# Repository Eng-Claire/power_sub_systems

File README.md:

Welcome to the MicroMouse project kiCAD files of Chidochashe Kufakunesu ( KFKCHI001) and Danella Oelofse ( OLFDAN001 )

The folder titled 'FinalMicroMouseFiles' is the final version of our project and the version that was submitted to UCT. It includes a screenshot of the JLCPCB cart, the BOM, the positions file, as well as the gerber and drill files from kiCAD.

The zip folder is the kiCAD gerber files that were submitted to JLCPCB for manufacturing.

The pdf entitled 'FinalSchematic' is the schematic of our entire solution for the power subsystem.

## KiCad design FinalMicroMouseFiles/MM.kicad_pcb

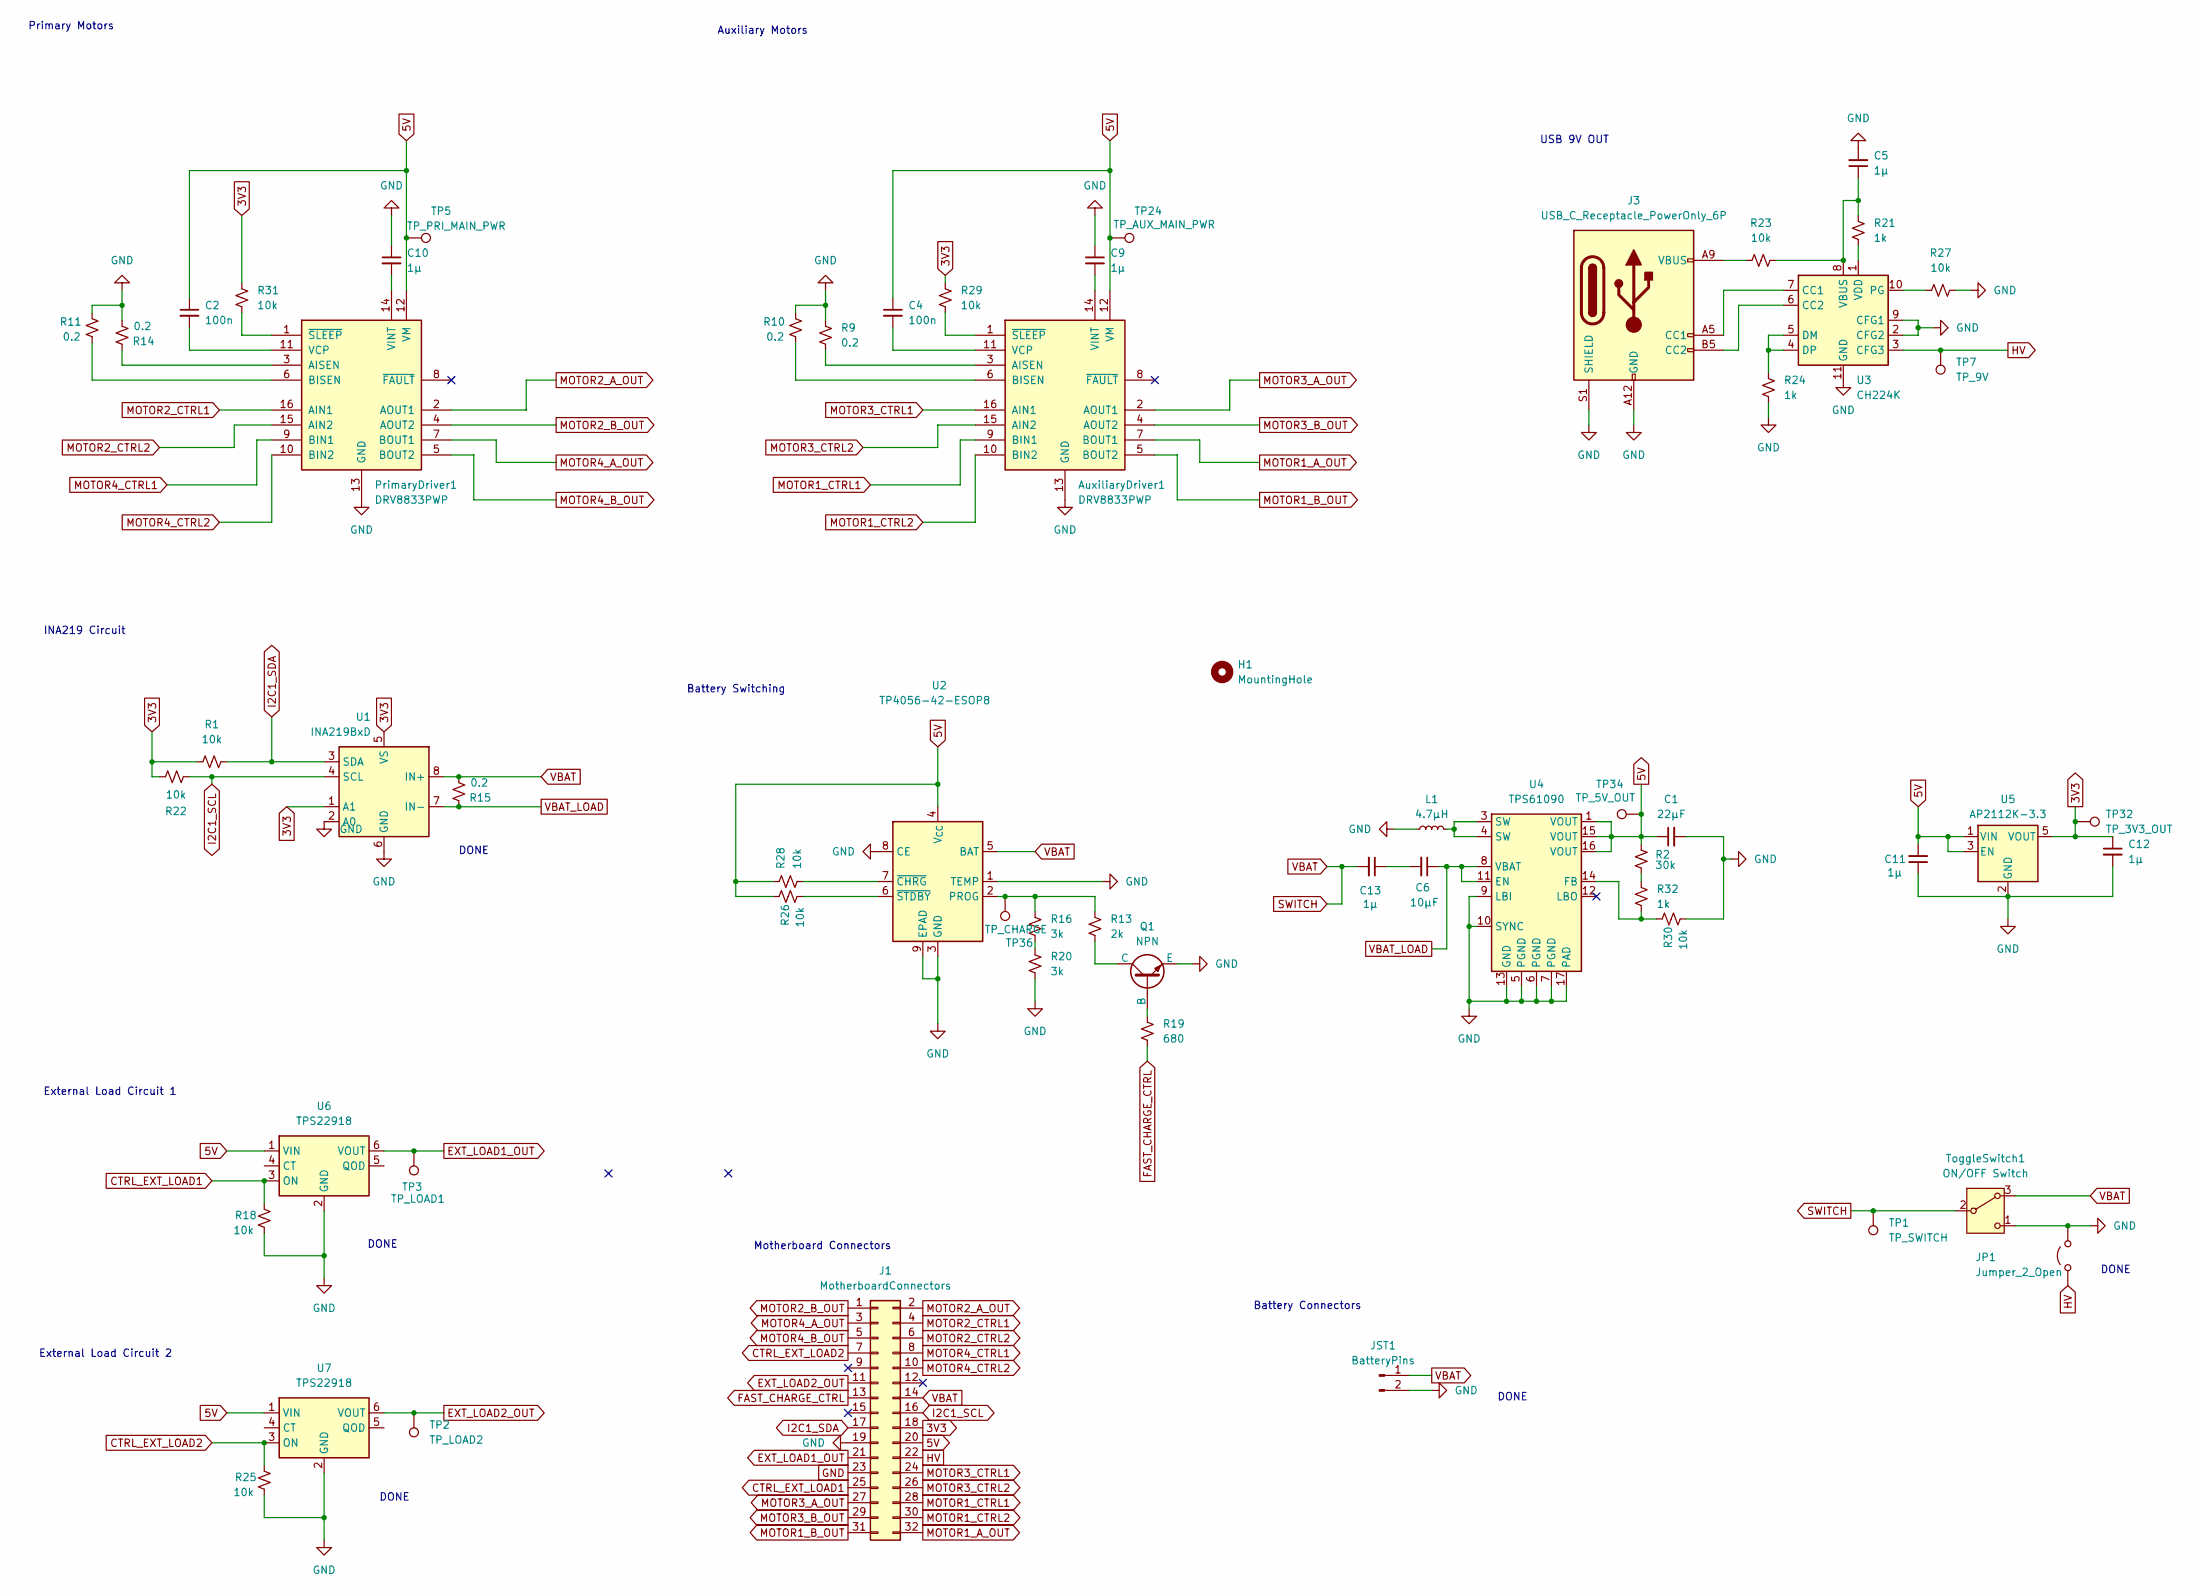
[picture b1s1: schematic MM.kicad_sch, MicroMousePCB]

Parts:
AuxiliaryDriver1: DRV8833PWP; TSSOP-16-1EP_4.4x5mm_P0.65mm_EP3x3mm_ThermalVias; LCSC C50506
C1: 22µF; C_0805_2012Metric_Pad1.18x1.45mm_HandSolder; LCSC C45783
C2, C4: 100n; C_0402_1005Metric; LCSC C1525
C5, C9, C10, C11, C12, C13: 1μ; C_0504_1310Metric_Pad0.83x1.28mm_HandSolder; LCSC C15849
C6: 10µF; C_1206_3216Metric_Pad1.33x1.80mm_HandSolder; LCSC C13585
H1: MountingHole; MountingHole_3.2mm_M3_DIN965_Pad
J1: MotherboardConnectors; PinHeader_2x16_P2.54mm_Vertical
J3: USB_C_Receptacle_PowerOnly_6P; USB_C_Receptacle_GCT_USB4125-xx-x-0190_6P_TopMnt_Horizontal; LCSC C668623
JP1: Jumper_2_Open; TestPoint_2Pads_Pitch2.54mm_Drill0.8mm
JST1: BatteryPins; JST_PH_B2B-PH-K_1x02_P2.00mm_Vertical; LCSC C157955
L1: 4.7µH; L_0603_1608Metric_Pad1.05x0.95mm_HandSolder; LCSC C114862
PrimaryDriver1: DRV8833PWP; TSSOP-16-1EP_4.4x5mm_P0.65mm_EP3x3mm_ThermalVias; LCSC C50506
Q1: NPN; TO-92; LCSC C5330385
R1, R18, R22, R23, R25, R26, R27, R28, R29, R30, R31: 10k; R_0805_2012Metric_Pad1.20x1.40mm_HandSolder; LCSC C17414
R2: 30k; R_0603_1608Metric_Pad0.98x0.95mm_HandSolder; LCSC C22984
R9, R10, R11, R14, R15: 0.2; R_0805_2012Metric; LCSC C2934262
R13: 2k; R_0603_1608Metric_Pad0.98x0.95mm_HandSolder; LCSC C22975
R16, R20: 3k; R_0603_1608Metric_Pad0.98x0.95mm_HandSolder; LCSC C4211
R19: 680; R_0603_1608Metric_Pad0.98x0.95mm_HandSolder; LCSC C23228
R21, R24, R32: 1k; R_0402_1005Metric; LCSC C11702
TP1: TP_SWITCH; TestPoint_Pad_D2.0mm
TP2: TP_LOAD2; TestPoint_Pad_D2.0mm
TP3: TP_LOAD1; TestPoint_Pad_D2.0mm
TP5: TP_PRI_MAIN_PWR; TestPoint_Pad_D2.0mm
TP7: TP_9V; TestPoint_Pad_D2.0mm
TP24: TP_AUX_MAIN_PWR; TestPoint_Pad_D2.0mm
TP32: TP_3V3_OUT; TestPoint_Pad_D2.0mm
TP34: TP_5V_OUT; TestPoint_Pad_D2.0mm
TP36: TP_CHARGE; TestPoint_Pad_D2.0mm
ToggleSwitch1: ON/OFF Switch; SW_SPDT_CK_JS102011SAQN; LCSC C1788492
U1: INA219BxD; SOIC-8-1EP_3.9x4.9mm_P1.27mm_EP2.29x3mm; LCSC C138706
U2: TP4056-42-ESOP8; SOIC-8-1EP_3.9x4.9mm_P1.27mm_EP2.41x3.3mm_ThermalVias; LCSC C16581
U3: CH224K; SSOP-10-1EP_3.9x4.9mm_P1mm_EP2.1x3.3mm; LCSC C970725
U4: TPS61090; Texas_RSA_VQFN-16-1EP_4x4mm_P0.65mm_EP2.7x2.7mm_ThermalVias; LCSC C206167
U5: AP2112K-3.3; SOT-23-5; LCSC C3021085
U6, U7: TPS22918; SOT-23-6; LCSC C131941

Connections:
3V3: C12.1, J1.18, R1.1, R22.2, R29.1, R31.1, TP32.1, U1.1 (A1), U1.5 (VS), U5.5 (VOUT)
5V: AuxiliaryDriver1.12 (VM), C1.1, C2.1, C4.1, C11.2, J1.20, PrimaryDriver1.12 (VM), R2.1, R26.1, R28.1, TP5.1, TP24.1, TP34.1, U2.4 (V_{CC}), U4.1 (VOUT), U4.15 (VOUT), U4.16 (VOUT), U5.1 (VIN), U5.3 (EN), U6.1 (VIN), U7.1 (VIN)
CTRL_EXT_LOAD1: J1.25, R18.1, U6.3 (ON)
CTRL_EXT_LOAD2: J1.7, R25.1, U7.3 (ON)
EXT_LOAD1_OUT: J1.21, TP3.1, U6.6 (VOUT)
EXT_LOAD2_OUT: J1.11, TP2.1, U7.6 (VOUT)
FAST_CHARGE_CTRL: J1.13, R19.2
GND: AuxiliaryDriver1.13 (GND), AuxiliaryDriver1.17 (GND), C1.2, C5.2, C9.1, C10.1, C11.1, C12.2, J1.19, J1.23, J3.A12 (GND), J3.B12 (GND), J3.S1 (SHIELD), JP1.2 (B), JST1.2, L1.1, PrimaryDriver1.13 (GND), PrimaryDriver1.17 (GND), Q1.3 (E), R9.2, R10.2, R11.2, R14.1, R18.2, R20.2, R24.2, R25.2, R27.2, R30.2, ToggleSwitch1.1 (C), U1.2 (A0), U1.6 (GND), U2.1 (TEMP), U2.3 (GND), U2.8 (CE), U2.9 (EPAD), U3.2 (CFG2), U3.9 (CFG1), U3.11 (GND), U4.5 (PGND), U4.6 (PGND), U4.7 (PGND), U4.9 (LBI), U4.10 (SYNC), U4.13 (GND), U4.17 (PAD), U5.2 (GND), U6.2 (GND), U7.2 (GND)
HV: J1.22, JP1.1 (A), TP7.1, U3.3 (CFG3)
I2C1_SCL: J1.16, R22.1, U1.4 (SCL)
I2C1_SDA: J1.17, R1.2, U1.3 (SDA)
MOTOR1_A_OUT: AuxiliaryDriver1.7 (BOUT1), J1.32
MOTOR1_B_OUT: AuxiliaryDriver1.5 (BOUT2), J1.31
MOTOR1_CTRL1: AuxiliaryDriver1.9 (BIN1), J1.28
MOTOR1_CTRL2: AuxiliaryDriver1.10 (BIN2), J1.30
MOTOR2_A_OUT: J1.2, PrimaryDriver1.2 (AOUT1)
MOTOR2_B_OUT: J1.1, PrimaryDriver1.4 (AOUT2)
MOTOR2_CTRL1: J1.4, PrimaryDriver1.16 (AIN1)
MOTOR2_CTRL2: J1.6, PrimaryDriver1.15 (AIN2)
MOTOR3_A_OUT: AuxiliaryDriver1.2 (AOUT1), J1.27
MOTOR3_B_OUT: AuxiliaryDriver1.4 (AOUT2), J1.29
MOTOR3_CTRL1: AuxiliaryDriver1.16 (AIN1), J1.24
MOTOR3_CTRL2: AuxiliaryDriver1.15 (AIN2), J1.26
MOTOR4_A_OUT: J1.3, PrimaryDriver1.7 (BOUT1)
MOTOR4_B_OUT: J1.5, PrimaryDriver1.5 (BOUT2)
MOTOR4_CTRL1: J1.8, PrimaryDriver1.9 (BIN1)
MOTOR4_CTRL2: J1.10, PrimaryDriver1.10 (BIN2)
unnamed: AuxiliaryDriver1.3 (AISEN), R9.1
unnamed: AuxiliaryDriver1.6 (BISEN), R10.1
unnamed: AuxiliaryDriver1.11 (VCP), C4.2
unnamed: AuxiliaryDriver1.14 (VINT), C9.2
unnamed: AuxiliaryDriver1.1 (~SLEEP), R29.2
unnamed: C6.2, C13.1
unnamed: J3.A5 (CC1), U3.7 (CC1)
unnamed: J3.B5 (CC2), U3.6 (CC2)
unnamed: J3.A9 (VBUS), J3.B9 (VBUS), R23.1
unnamed: L1.2, U4.3 (SW), U4.4 (SW)
unnamed: PrimaryDriver1.3 (AISEN), R14.2
unnamed: PrimaryDriver1.6 (BISEN), R11.1
unnamed: C2.2, PrimaryDriver1.11 (VCP)
unnamed: C10.2, PrimaryDriver1.14 (VINT)
unnamed: PrimaryDriver1.1 (~SLEEP), R31.2
unnamed: Q1.2 (B), R19.1
unnamed: Q1.1 (C), R13.2
unnamed: R2.2, R32.1
unnamed: R16.2, R20.1
unnamed: R13.1, R16.1, TP36.1, U2.2 (PROG)
unnamed: R28.2, U2.7 (~CHRG)
unnamed: R26.2, U2.6 (~STDBY)
unnamed: R24.1, U3.4 (DP), U3.5 (DM)
unnamed: R27.1, U3.10 (PG)
unnamed: C5.1, R21.1, R23.2, U3.8 (VBUS)
unnamed: R21.2, U3.1 (VDD)
unnamed: R30.1, R32.2, U4.14 (FB)
SWITCH: C13.2, J1.14, JST1.1, R15.1, TP1.1, ToggleSwitch1.2 (B), ToggleSwitch1.3 (A), U1.8 (IN+), U2.5 (BAT)
VBAT_LOAD: C6.1, R15.2, U1.7 (IN-), U4.8 (VBAT), U4.11 (EN)

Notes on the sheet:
Primary Motors
DONE
External Load Circuit 1
Motherboard Connectors
INA219 Circuit
Battery Connectors
Auxiliary Motors
External Load Circuit 2
USB 9V OUT
Battery Switching

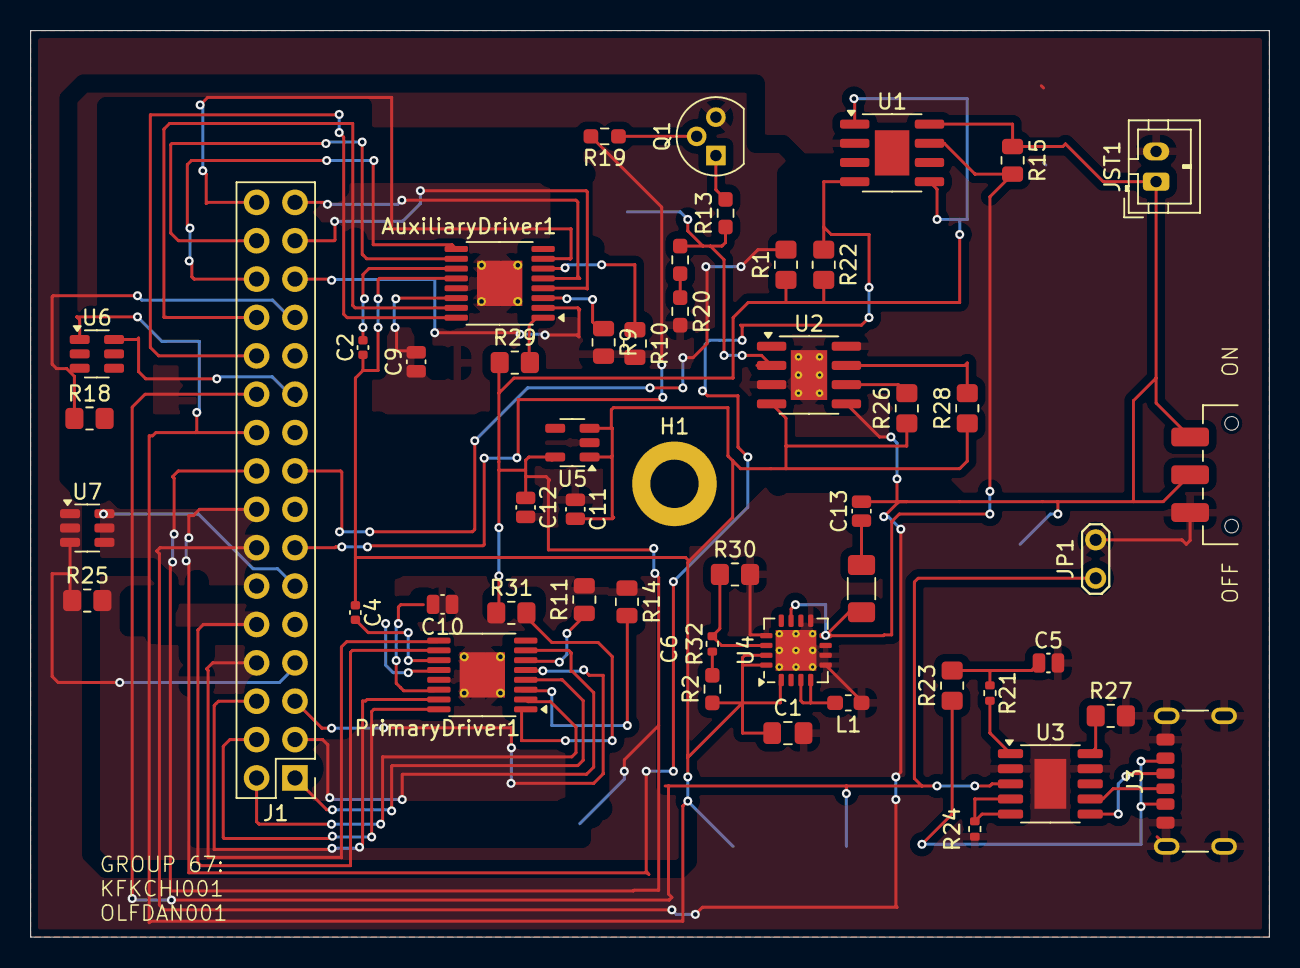
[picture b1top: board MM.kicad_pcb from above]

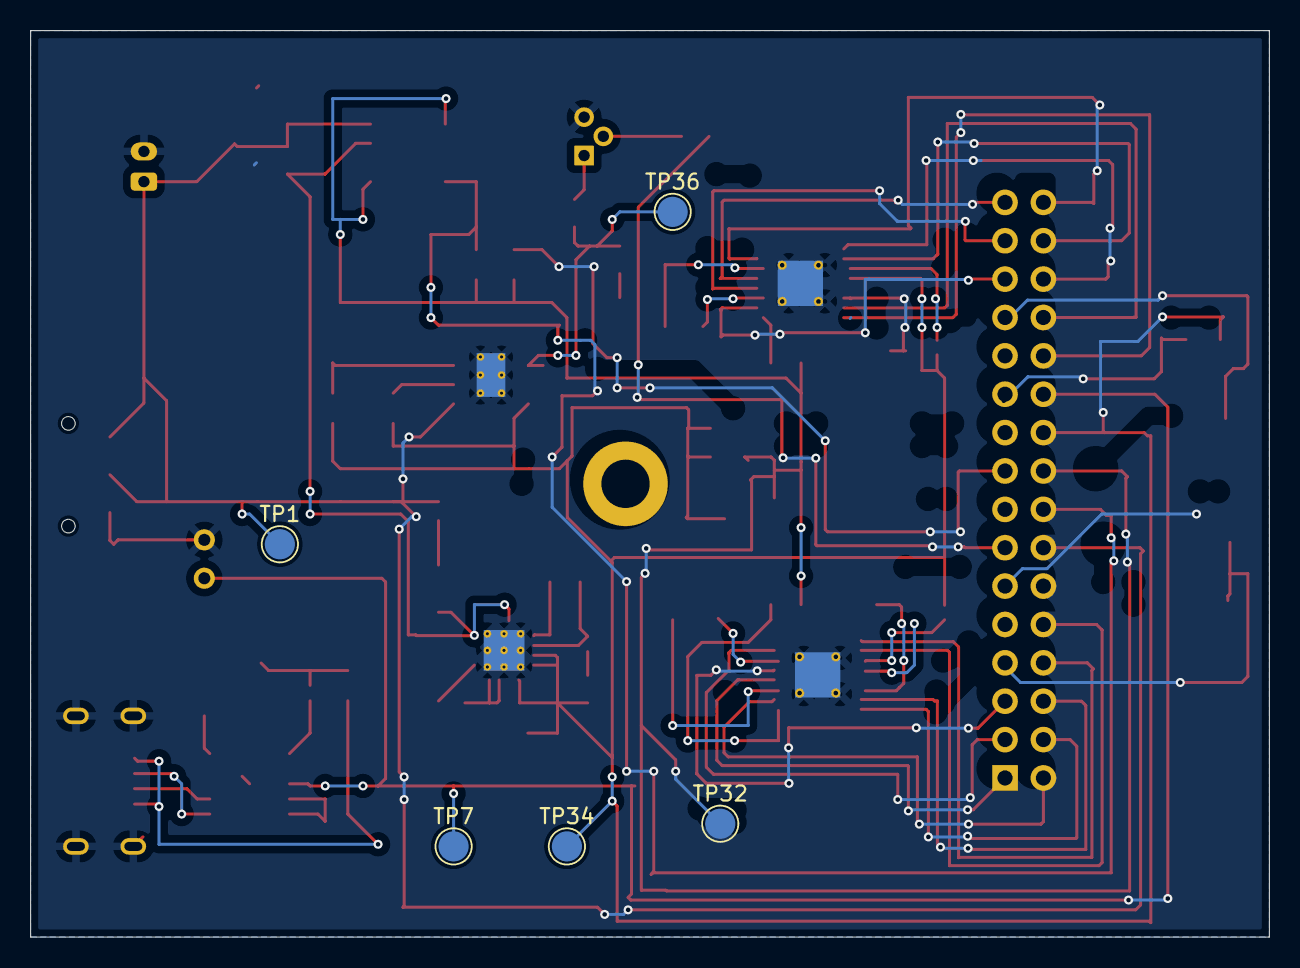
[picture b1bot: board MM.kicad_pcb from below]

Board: 2 copper layers, 82.0 x 60.0 mm, 56 parts (5 on the bottom side), 56 nets.

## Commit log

2025-04-25 Create FinalMicroMouseFiles
2025-04-25 Added Final MM kiCAD files
